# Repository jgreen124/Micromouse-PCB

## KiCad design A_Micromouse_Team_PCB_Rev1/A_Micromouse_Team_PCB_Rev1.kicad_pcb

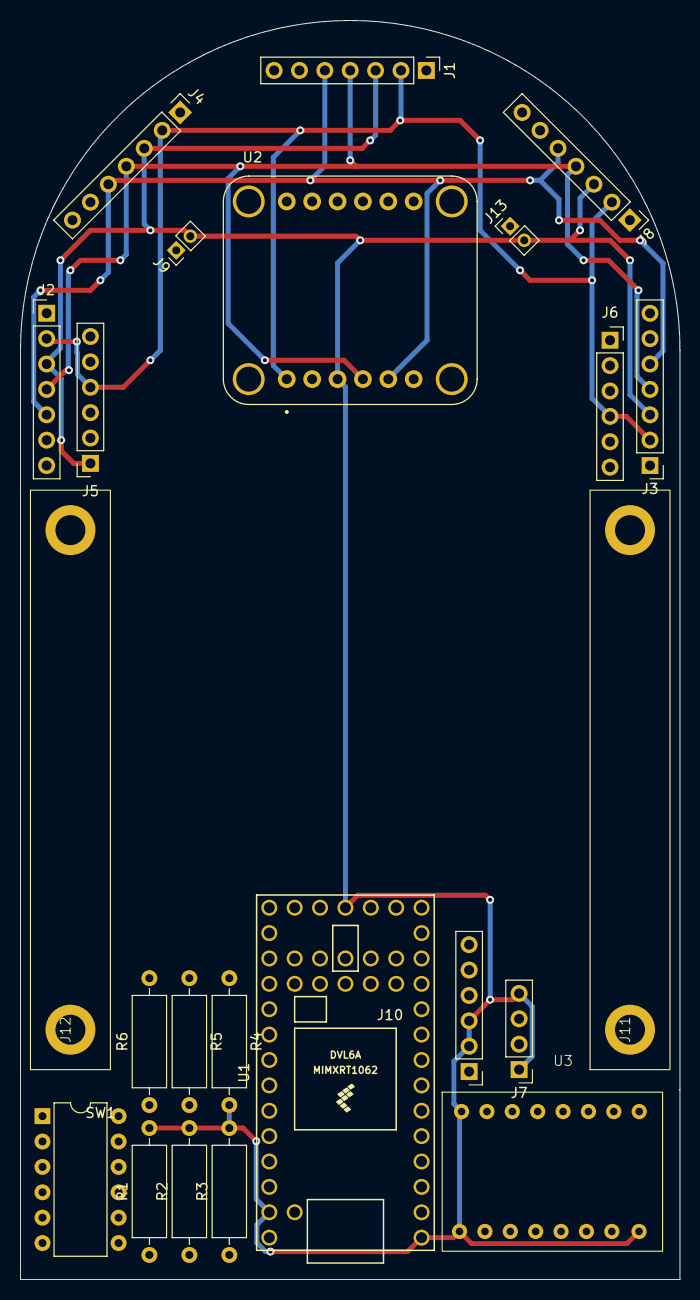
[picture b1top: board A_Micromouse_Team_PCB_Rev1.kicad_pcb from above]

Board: 2 copper layers, 66.0 x 126.0 mm, 23 parts (0 on the bottom side), 34 nets.

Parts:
J1: TOF2; PinHeader_1x07_P2.54mm_Vertical
J2: locked; PinHeader_1x07_P2.54mm_Vertical
J3: TOF4; PinHeader_1x07_P2.54mm_Vertical
J4: TOF5; PinHeader_1x07_P2.54mm_Vertical
J5: Motor1; PinSocket_1x06_P2.54mm_Vertical
J6: Motor2; PinSocket_1x06_P2.54mm_Vertical
J7: NeoPixel; PinHeader_1x04_P2.54mm_Vertical
J8: TOF1; PinHeader_1x07_P2.54mm_Vertical
J9, J13: Battery; PinHeader_1x02_P2.00mm_Vertical
J10: 5V->12V; PinHeader_1x06_P2.54mm_Vertical
J11, J12: MotorCageMount; motorMount
R1, R2, R3, R4, R5, R6: R_US; R_Axial_DIN0309_L9.0mm_D3.2mm_P12.70mm_Horizontal
SW1: SW_DIP_x06; DIP-12_W7.62mm
U1: Teensy4.0; Teensy40
U2: IMU; MODULE_4754
U3: MotorController

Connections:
+3.3V: R5.2, R6.2, U1.16 (3V3), U1.31 (3V3), U3.19 (STBY)
+5V: J1.2, J2.2, J3.2, J4.2, J5.4, J6.4, J7.3, J8.2, SW1.7, SW1.8, SW1.9, SW1.10, SW1.12, U1.33 (VIN), U2.3 (VDD), U3.20 (VCC)
+5VD: J10.4, J10.5, J13.1
+12V: SW1.11, U3.24 (VM1)
GND: J1.3, J2.3, J3.3, J4.3, J5.1, J6.1, J7.1, J7.4, J8.3, J9.2, J10.2, J10.3, J13.2, R1.2, R2.2, R3.2, R4.2, U1.1 (GND), U1.17 (GND), U1.32 (GND), U2.2 (GND), U3.18 (GND)
unnamed: J5.2, U1.9 (7_RX2_OUT1A)
unnamed: J5.3, U1.10 (8_TX2_IN1)
unnamed: J5.5, U3.7 (BO2)
unnamed: J5.6, U3.11 (BO1)
unnamed: J6.2, U1.11 (9_OUT1C)
unnamed: J6.3, U1.12 (10_CS_MQSR)
unnamed: J6.5, U3.5 (AO2)
unnamed: J6.6, U3.1 (AO1)
unnamed: J7.2, U1.29 (22_A8_CTX1)
unnamed: J9.1, SW1.1
unnamed: J10.1, SW1.2
unnamed: J10.6, U1.4 (2_OUT2)
unnamed: U1.2 (0_RX1_CRX2_CS1), U3.21 (AIN1)
unnamed: U1.3 (1_TX1_CTX2_MISO1), U3.22 (AIN2)
unnamed: U1.13 (11_MOSI_CTX1), U3.23 (PWMA)
unnamed: U1.14 (12_MISO_MQSL), U3.15 (PWMB)
unnamed: U1.20 (13_SCK_CRX1_LED), U3.17 (BIN1)
unnamed: U1.22 (15_A1_RX3_SPDIF_IN), U3.16 (BIN2)
SCL: J1.5, J2.5, J3.5, J4.5, J8.5, R6.1, U1.23 (16_A2_RX4_SCL1), U2.19 (COM1)
SDA: J1.4, J2.4, J3.4, J4.4, J8.4, R5.1, U1.24 (17_A3_TX4_SDA1), U2.20 (COM0)
SW1: R4.1, SW1.3, U1.25 (18_A4_SDA0)
SW2: R3.1, SW1.4, U1.26 (19_A5_SCL0)
SW3: R2.1, SW1.5, U1.27 (20_A6_TX5_LRCLK1)
SW4: R1.1, SW1.6, U1.28 (21_A7_RX5_BCLK1)
TOF1: J8.6, U1.5 (3_LRCLK2)
TOF2: J1.6, U1.6 (4_BCLK2)
TOF3: J2.6, U1.7 (5_IN2)
TOF4: J3.6, U1.8 (6_OUT1D)
TOF5: J4.6, U1.21 (14_A0_TX3_SPDIF_OUT)

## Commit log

2024-01-24 second commit
2024-01-25 added teensy footprint
2024-01-25 updated schematic with teensy
2024-01-25 commit from a different branch
2024-01-31 changed Net Classes
2024-02-06 fixing bad repo management
2024-02-06 from main
2024-02-06 fixed repo
2024-02-06 rearranged schematic to make more legible
2024-02-06 made schematic more readable
2024-02-06 finished revamped schematic
2024-02-06 revamped schematic
2024-02-07 checked all footprints and created a max footprint
2024-02-08 started footprint layout
2024-02-15 finished pcb layout (hopefully)
